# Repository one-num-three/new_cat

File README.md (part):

# 猫鼠行动 · 微信试点

## 小程序星露谷 16-bit UI 改版与上线前合规补齐（2026-11-27，前端本地完成）

完成微信小程序全页面视觉重构与上线前合规打磨（主包与 `room-tools` / `field-editor` 等现有分包，不改动服务端规则或 `hardware/`）：
- **星露谷 16-bit 像素 UI 与视觉细节重构**：建立统一像素木框/羊皮纸与夜间营火主题（`utils/sdv-theme.wxss`、`utils/sdv-borders.wxss`、`components/sdv-modal/`、`assets/sdv-v1/`），替换首页 3:2 像素头图并优化创建/准备/对局/导览/结算及分包页的层次、字号等宽数字、禁用按钮对比度与夜间模式可读性。
- **隐私合规与户外安全门禁**：移除首页冷启动自动读取剪贴板，改为用户手动点击粘贴并接入 `getPrivacySetting` / `requirePrivacyAuthorize` / `openPrivacyContract`；在创建房间、输入房间码加入与扫码加入前增加户外安全与隐私确认弹窗。
- **对局定位提示、残局清理与 7 日本地战绩页**：对局地图页增加“仅前台定位”提醒横幅及设置引导；首页自动清理已失效 `v2RoomId` 残留；新增分包本地 7 日战绩页（`room-tools/pages/history/`）并自动归档最近战绩；通过 `sitemap.json` 禁止索引调试台/标定等非业务页面。
- **验证范围与待验项**：本地 WXML/WXSS 编译、包体体积门禁（`rawLocalBytes.main < 1,500,000 B`，各分包 `< 2,097,152 B`）以及客户端/界面自动化回归通过；真机定位/相机/海报导出/安全区实测及微信开发者工具上传发布尚未执行。

## 猫鼠手环硬件 V1.5 EVT-A（2026-11-28，Strap-Halo 双版本 17 件 3D CAD + 磁吸四线 FPC + 4 层 KiCad 10 主板）

已完成 **EVT-A 机电变更同步**：包含 **Strap-Halo 腕带光环版双版本 17 零件参数化 3D CAD / Autodesk Fusion 360 工程（量产针扣版 + EVT `120–200 mm` 非对称低遮挡魔术贴简版）**、**磁吸四线 C 弯柔性转接板（0 ERC / 0 DRC，已导出打样 Gerber ZIP）**、**Strap-Halo 28.4×35.4 mm 四层 KiCad 10 主板工程（含 BLE 真实铣空槽）**、虚拟烧录仿真与产品报价分析（目录 `hardware/`）。
- **EVT-A 双版本 17 零件 3D CAD & Fusion 360 (`cad/output/CatMouseBand_V15_StrapHalo.step` · `CatMouseBand_V15_Velcro_Lite.step`)**：顶壳抬高 `+0.35 mm`（主机厚 `12.15 mm`，`ESP32-C3-MINI-1` 上方留 `0.80 mm` 净空至 NFC 铁氧体）、主板开真实 BLE 天线铣空槽（`X ∈ [-8.9, +5.5], Y ≤ -12.15`）、闭合 Hirose `FH19C-4S-0.5SH(10)` 4-Pin ZIF 与 `2.50×0.20×3.60 mm` PI 补强舌、完整建模 `17_Pogo_Flex_Interposer` 绕开 `1027` 马达（最小名义间隙 `0.125 mm`）。两版均通过 **17/17 合法 B-Rep 与 `0.000 mm³` 零碰撞校验**（针扣版 `33.06 g` / 魔术贴简版 `35.07 g`，后者实现 `136–200 mm` 腕围 `0%` 零遮光）。
- **EVT-A 磁吸四线 FPC (`pcb/catmouse-band-v15-pogo-flex/`)**：4 线（5V / GND / USB D− / D+）绕开马达，ERC=0、DRC=0、未连通=0，已导出工程打样资料 `Pogo-Flex-EVT-A-Gerber.zip`。
- **EVT-A 四层主板 (`pcb/catmouse-band-v15-strap-halo/`)**：与 3D 共享 `strap_halo_geometry.py` 轮廓，ERC=0，固件物理引脚 13/13 一致（尚有 10 项布线与 17 项阻值配料待闭合后投板）；已将 `hardware` 纳入 `project.config.json` 打包忽略项，不影响现有小程序主包。

入口：[硬件总览](hardware/README.md) · [EVT-A 机电变更记录](hardware/docs/Strap-Halo-EVT-A-机电变更.md) · [PCB 与 3D 结构协同布局规范](hardware/docs/PCB与3D结构协同布局规范.md) · [3D CAD & Fusion 360 双版本工程](hardware/cad/README.md) · [EVT-A 内部连接微距详图](hardware/cad/renders/cad_06_fpc_connection_detail.png) · [ECAD/MCAD 布局蓝图](hardware/cad/renders/cad_05_ecad_mcad_layout_blueprint.png) · [120–200mm 魔术贴遮盖分析图](hardware/cad/renders/cad_velcro_02_wrist_occlusion_analysis.png) · [磁吸四线 FPC 打样包](hardware/pcb/catmouse-band-v15-pogo-flex/Pogo-Flex-EVT-A-Gerber.zip) · [EVT-A 主板检查报告](hardware/pcb/catmouse-band-v15-strap-halo/review/audit.json)。

## 当前位置与后台授权（2026-11-04，前端修订）

通用范围编辑首次打开/切换地图时优先居中本人，拒绝定位仍可手动框选；已有集合点和手动操作不被迟到GPS覆盖。对局显式申请前台及后台定位授权，拒绝/接口不可用时降级前台。234项回归与编译/发行目录核验通过。[当前前端与真机待验步骤](reports/2026-11-04/current-location-background-v1/README.md)。账号后台接口仍需开通；本轮未微信上传或宣称真机锁屏通过。下方保留历史记录。

## 通用微信实时地图（2026-11-04，本地实现）

创建活动可直接点“使用实时地图”，选集合点并框选多边形，不再要求预制美术图或校区标定；原生对局地图支持现有角色授权、扫码抓捕、结算和轨迹导出。230项测试通过，前后端需配套部署。Git分支`codex/general-native-map`。[使用与验证说明](reports/2026-11-04/native-map-v1/README.md)。

## GPS精度放宽至50米（2026-10-23，已部署）

正式服务器已切换GPS50修订，版本仍0.6.1，准备/抓捕精度门槛≤50米。5秒新鲜度、双方坐标距离≤50米及动态码保持。公网健康检查与隔离PG验收通过；前端文案需重新编译/上传。[部署证据及最新前端目录](reports/2026-10-23/gps-threshold-50-v1/README.md)。

## 0.6.1 已部署与移动界面修订（2026-10-23）

后端0.6.1已上线，228项回归与模板/样式编译通过；修正定位信号宽度、按钮对齐、长文字、小屏大字号和安全区。完整前端：`reports/2026-10-23/deploy-0.6.1-v1/frontend-final/MODIFIED_FILE`。微信上传待开发者工具内确认，尚未公开发布；[交付与48张截图](reports/2026-10-23/deploy-0.6.1-v1/README.md)。下方保留历史状态。

## GitHub代码同步（2026-10-23）

当前代码包含候选API0.6.1及微信端的轨迹海报、保存/转发、鼠队视野共享、定位质量小信号，前后端保留在同一个仓库。本轮重新运行227项自动回归全部通过；[同步前验证](reports/2026-10-23/github-sync-v1/verification.json)。GitHub代码同步不等于服务器部署或微信上传；真机室外定位、相册保存/发送等仍需设备验证。以下保留各轮历史记录。

## 定位质量小信号（2026-10-22，本地完成）

地图/准备页增加四格定位指标与`±12m`精度估计，点开可查看原因：≤5/≤10/≤25/>25米依次4/3/2/1格；过期、权限、网络等灰显。25米服务端校验和5秒位置有效期保持，不新增定位请求。227项回归通过；[显示预览与验证](reports/2026-10-22/location-signal-v1/index.html)，非微信截图，真机待验。最新完整前端reports/2026-10-22/location-signal-v1/release-verified/MODIFIED_FILE；本次未部署或上传。

## 海报保存与转发（2026-10-22，本地完成）

结算→本人轨迹→生成海报；底部固定保存相册/转发入口，支持点图预览、长按操作。取消、权限失败和成功均有反馈；原生菜单使用期间保留临时文件，切页/身份变化防旧回调。220项回归通过，手机相册/实际发送仍未验；本次未部署或上传。[可保存的模拟轨迹PNG及验证](reports/2026-10-22/poster-save-share-v1/index.html)。最新完整前端：reports/2026-10-22/poster-save-share-v1/release-verified/MODIFIED_FILE；API仍为本地候选0.6.1，历史记录如下。

## 最新候选0.6.1：轨迹亮点（2026-10-21，未部署/上传）

本人轨迹海报新增透明起终点旗子、“跑得最快”和鼠身份的“离猫最近”真实数据气泡；位置由有效记录计算，不预画。近猫摘要由服务端赛后授权派生，普通玩家不收到猫坐标或隐藏路线。数据不足省略。

最新四张左右透明气泡已接入，并修正起点遮挡：亮点后画旗子，气泡按完整旗框优先换向、再移位，文字/旗子零交叠。216项回归通过，三地图六面旗像素校验通过。[最新对照预览](reports/2026-10-21/track-highlights-layer-v2/index.html) · [代码/验证说明](reports/2026-10-21/track-highlights-layer-v2/README.md)。微信原生页面仍未验收（上一轮工具受阻，本修订未重试）；预览为桌面Canvas，非微信截图/真人记录。完整前端：`reports/2026-10-21/track-highlights-layer-v2/release-verified/MODIFIED_FILE`。旧交付保留，下方0.6.0为历史记录。

## 最新本地候选0.6.0（2026-10-21，未部署/上传）

新增房主“鼠队视野共享”设置、赛后本人/房主全员轨迹导出，以及用户确认的不规则草地边框海报（玄武湖、九龙湖、四牌楼）。使用真实本局记录，不预画路线或套用示例数字；地图等比，原画保留。开局冻结设置/标定，历史结果不覆盖。

入口：房间→玩法设置；结算→我的行动轨迹与导出→生成我的轨迹海报。当前线上0.5.2不支持新接口，须前后端配套升级。

[使用规则和现场步骤](TRACKS_AND_TEAM_VISION.md) · [实际微信预览](reports/2026-10-21/tracks-team-vision-v1/index.html) · [启动与验证记录](reports/2026-10-21/tracks-team-vision-v1/README.md)。最终完整前端目录：`reports/2026-10-21/tracks-team-vision-v1/release-verified/MODIFIED_FILE`。209项回归通过；真机保存/分享、后台权限及新公网压测未验。下方内容为各轮历史记录。

## 代码质量复核（2026-10-21）

地图原图保留，按用户决定不处理单张图片200 K建议项。已开启组件按需注入，微信工具重新扫描该项通过；字体原始字节不变，改为app.wxss全局声明。主包原始文件989,713 B；微信依赖分析约943 KB，但质量面板的1.5 M项仍未通过，原因尚未确定，不把源码统计当成平台通过。用户决定停止追查该提示。

当前完整前端目录：`reports/2026-10-21/package-quality-v2/release/MODIFIED_FILE`，包含app.wxss和全部分包。196项回归及逐入口编译通过；本轮没有上传或发布。[复核记录](reports/2026-10-21/package-quality-v2/README.md)。下方为历史记录。

## 主包已降至约0.99MB（2026-10-21，本地完成）

工程及最终目录包主包原始文件均为989,574B，低于更严格的1,500,000B上限，余510,426B。玄武湖原图按需分包，图片尺寸/字节/标定SHA与美术不变，根文档和未引用旧API不再上传；打包与回归增加主包硬门禁和运行依赖核验。196项回归、17WXML/21WXSS编译、微信MCP冷加载创建页/玄武湖/九龙湖及切回通过。不是微信上传后包体或真机公网下载验收，本轮未上传、发布或部署。

工程仍打开根目录。最新完整前端目录：`reports/2026-10-21/main-package-v1/release-verified/MODIFIED_FILE`，需要保留所有分包。[体积、截图与复核命令](reports/2026-10-21/main-package-v1/README.md)。以下日期条目保留历史状态。

## 本地新增：对局后台定位（2026-10-20，API 0.5.3 候选）

已接微信后台定位：本局参与期间切后台保留定位和授权连接；被捕、退出、取消或终局后停止；返回前台保持同一身份和对局，不重复启动轮询。权限不足时明确降级为前台模式。新增对局绑定的位置样本门禁，无表迁移，猫鼠行动规则不变。

193/193 回归、官方编译及 MCP 隐藏/恢复/被捕清理验证通过；MCP 模拟后台授权和生命周期，不代表真机锁屏通过。**用户确认账号尚未开通 startLocationUpdateBackground，线上仍 0.5.2，本候选未部署或上传。** 配置入口、目录包、截图和权限获批后的手机测试见 [后台定位交付](reports/2026-10-20/background-location-v1/README.md)。下方各日期记录保留历史状态。

## 当前服务：API0.5.2已部署（2026-10-19）

真实HTTPS/WSS已更新为0.5.2，支持reinforce-v2动态捕获目标、fresh-v1重新准备及认证快照viewerId。原房间/会话保留，切换前0活跃局；数据库备份已独立恢复核验。当前微信工程及配套前端目录版同步为本次源码，测试身份关闭。微信开发版本上传状态以 [本次部署证据](reports/2026-10-19/deploy-0.5.2-v1/README.md) 为准；正式审核发布须区分记录。

运行工程仍为 `D:\cat-mouse-miniprogram`，目录交付为 `reports/2026-10-19/deploy-0.5.2-v1/frontend-final/MODIFIED_FILE`。下方“尚未部署”描述保留其历史日期状态，由本节接续。

## 最新本地增量：动态捕获目标（2026-10-19，API 0.5.2）

中途补员采用 **reinforce-v2**：捕获目标始终为本局累计加入的鼠人数的60%，向上取整。标准8人2猫6鼠开局为4；第9人补鼠后为5，第10人补猫后仍为5；补到12人3猫9鼠后为6。右上角分母由同一服务端事务更新，经授权WebSocket同步给所有人，断线恢复使用最新快照。原阵营和本局截止时间不变。

入房成功即计入，30秒内定位入场；被捕、主动退出、入场超时和断线均不减少累计鼠人数，原身份重连不重复增加目标。已确认终局不因后来的加入而重开或改写。新增猫更新人数，鼠人数未变时60%规则的目标保持不变。此规则覆盖历史 reinforce-v1 的固定目标约定，仍是待场地验证的试点参数。

本地使用原启动方式与数据库，无表迁移；线上仍0.5.0，本轮不部署或微信发布。验证与MCP截图见 [动态目标说明](reports/2026-10-19/dynamic-target-v1/README.md)。下方各轮说明保留历史语义。

## 最新本地验证：扫码抓捕、全员结算与下一局（2026-10-19，API 0.5.1）

微信MCP已完成标准8人局：4次实际动态码PNG解码后的模拟扫码、8人一致猫胜、全员重新定位准备、新matchId及8人新阵营。21张原图逐一核对服务端viewerId、房主标志、角色、状态、进度与胜负；旧结果保持唯一且未覆盖。**181/181回归通过**，编译通过。[截图图集](reports/2026-10-19/mcp-capture-replay-v1/index.html) · [复现与验证范围](reports/2026-10-19/mcp-capture-replay-v1/README.md)。

修复终局旧ready残留、普通玩家无法回准备、抓捕提示被快照清除和旧会话快照/响应串入。新开局仍只允许房主；本地0.5.1新增fresh-v1准备约束及认证快照viewerId。**线上仍0.5.0，本轮修复尚未部署，前端未上传发布**。本次1个模拟器＋8条授权WS、模拟GPS/相机回传，不代表真机相机或公网验收。

## 当前交付：中途补入猫鼠与全员同步（2026-10-19）

本次新增微信MCP完整复验：标准8人开局后补入2人，10个授权连接的角色、状态和公共名单一致，已取得10个身份各自的实际页面截图；P09断线→失联暂停→原页自动重连→被捕房主恢复均通过。修复被捕房主恢复和旧会话快照保护，当前回归 **177/177**。本轮为1个模拟器＋10个WS、模拟GPS、本机隔离PGlite，不代表10台真机或公网验收。[本轮图集](reports/2026-10-19/mcp-join-reconnect-v1/index.html) · [复现方法与证据](reports/2026-10-19/mcp-join-reconnect-v1/README.md)。前端仍需本地编译预览，尚未上传发布。

后端 **0.5.0 已部署**。开局后新玩家按开局比例补入猫或鼠，30秒内定位入场；老玩家不重抽，开局捕获目标和截止时间不变。断线回来保留原阵营及被捕/退出状态，不能重进入房复活。新增试点策略登记为 reinforce-v1，基础pilot-0.3保留。

准备页和地图页共用实时WebSocket、断线轮询与重连；名单、阵营、在线/入场/出局、进度及结果统一同步，位置仍按权限裁剪。此前175项基线回归通过，真实PostgreSQL完成8人开局＋2人补入、10个授权WS一致快照；最新177项及MCP复验见上段。真机/现场平衡和本轮新负载验收未执行，前端尚未发布。

[本轮规则、配置与证据](reports/2026-10-19/late-join-sync-v1/README.md) · [微信MCP截图](reports/2026-10-19/late-join-sync-v1/index.html)。开发工具继续打开本仓库根目录并编译，真实房间码9D61CEDC51仍保留。

## 上一轮交付：真实地图服务、房间与邀请（2026-10-19，0.4.0）

后端 API **0.4.0** 已部署到 https://seu-link.fit/catmouse ，沿用真实微信登录与 PostgreSQL；正式默认8人2猫6鼠、捕获目标4，规则仍 pilot-0.3。服务端登记三处地图、修订与图层；房主可在开局前/终局后改校区、集合点、多边形范围。建房有持久化幂等回执，抓捕凭据绑定对局/目标/有效期并原子确认，超时可用同指令重试。

微信开发工具打开本仓库根目录。首页新增“扫码加入”，准备页提供微信分享与真实邀请二维码。普通邀请二维码须在本小程序内扫描，不是外部微信启动码。当前前端尚未上传/发布，手机需预览本工程。真实MCP联调房间码 **9D61CEDC51**，当前1/8人、未开始；没有向联系人发送分享。

173项回归通过，真实PostgreSQL隔离验收14项、备份恢复成功；官方16WXML/20WXSS编译通过。微信MCP已验证真实登录/建房/范围保存/邀请码解码和一次授权WSS联通，修复实际编辑面板裁切。真机相机、GPS、公网长时联机、微信上传包体仍待验。

完整启动/配置、截图、目录版交付与真机步骤见 [本轮说明](reports/2026-10-19/real-rooms-v1/README.md) 和 [MCP图集](reports/2026-10-19/real-rooms-v1/index.html)。以下旧章节保留各自日期与当时验证结论，当前状态以本节和RELEASE顶部为准。

## 集合点与多边形范围初始增量（2026-10-19，已由0.4.0接续）

- 创建活动 → **地图框选范围**；已有房间由房主点 **修改集合点与范围**。在真实地图依次选3–16个顶点，单独选集合点；点编号后可移动顶点，支持撤销/删除/重画、地图平移和缩放。
- 开局前或终局后可改；进行中和暂停时锁定。保存到服务端后全员重新定位、准备。原圆形场地兼容；新多边形同时用于越界裁决及原生/艺术/3D地图显示。
- 开发调试台新增「集合点与多边形 · 开发预览」，只验证交互，不读取GPS或提交服务器。
- 后端需 `/api/version` **0.3.3 / polygonVenues:true**；本轮仅本地实现，未部署或上传。使用与验证边界见 [交付说明](reports/2026-10-19/venue-boundary-v1/README.md)。

## 仓库结构与独立部署

前后端在同一仓库维护，分别运行和部署，保持接口、地图参考和规则变更同步：

| 目录 | 用途 |
| --- | --- |
| 根目录的 `app.*`、`pages/`、`components/`、`utils/` | 微信小程序；开发者工具打开仓库根目录 |
| `cat-mouse-server/` | 后端服务、共享规则/坐标模块与自动化回归；Docker构建目录也在这里 |
| `assets/`、`campus3d/`、`venue-maps/` | 客户端运行素材与按需资源分包 |
| `design/` | 设计原件、许可、地理参考及回归依赖；保留原始字节供SHA校验 |
| `scripts/`、`reports/` | 构建工具、审计与验证说明 |

GitHub同步保留源码、测试和必要原件；本机密钥、数据库、依赖缓存、压缩归档、重复交付副本与报告截图通过`.gitignore`排除，仍留在本地。报告中的历史截图/交付路径可能仅在原工作目录可用。真实配置从环境变量或未跟踪的`.env`加载，示例见`cat-mouse-server/.env.example`。后端独立部署不要求把微信前端放到服务器。

## 2026-10-19 · 微信日志排查与 3D 首次加载修复

模型描述改为可读取的 `campus3d/assets/campus-meta.bin`（UTF-8 JSON 内容），修复重新编译后 3D 加载失败；四个业务页补齐首帧字体参数。最新修复、重新编译后的实际截图与回归见 [排查记录](reports/2026-10-19/wechat-permission-diagnostics-v1/README.md)。此记录补充并更新下方首版 3D 交付；未上传或部署。

## 九龙湖 3D 视图更新 · 2026-10-19

当前工程已增加九龙湖第三种可切换视图：**像素地图 / 实时地图 / 3D校园**。打开本目录，编译后进入「场地地图→九龙湖→叠层图标→3D校园」；对局页也有同一入口。单指平移、双指缩放旋转，准星回到本人。3D 需要首开加载本地资源分包，真机仍需允许定位。

3D 使用提供的「已建与在建、去规划」Blender 模型，并有独立的近似定位参考；不是实测建筑/高度地图。原像素图及其控制网保留。模型说明见 [模型 README](design/models/jiulonghu-blender-v1/README.md)，验证记录见 `reports/2026-10-19/jiulonghu-3d-v1`。本次不修改服务端猫鼠行动规则，也未发布、上传或部署。

## 2026-10-18 九龙湖全校参考覆盖 v3

当前运行模型补齐外围8个道路路口/桥端参考点，共31控制点、53分区，完整覆盖保存的OSM校园多边形。运行投影检查86个独立校界顶点、沿界约5米采样和校内10米网格，无遗漏或图外位置；原23地标和梅园反馈坐标保持。模型与原画不等于实地测量，`fieldVerified=false`；定位覆盖边界也不是猫鼠行动活动范围。边界图、复核命令与证据见 [本轮说明](reports/2026-10-18/jiulonghu-campus-coverage-v3/README.md)。重新编译小程序即可使用，手机仍读取真实GCJ-02定位。

## 2026-10-18 九龙湖梅园定位覆盖修复

已复现并修复梅园7B附近“校区内却提示图片配准范围外”：补3个OSM/原画地标，将九龙湖控制网扩为23点/36分区，原画不变。开发调试台新增「九龙湖 · 电脑模拟本人定位」，仅电脑开发工具启用，明确标记模拟；手机仍采实际GPS。139项回归通过；详情与截图见 [本轮记录](reports/2026-10-18/jiulonghu-location-fix-v1/README.md)。

## 2026-10-17 地图余量与真机本人定位

艺术地图四边增加停留余量、阻尼与220ms回弹。「首页 → 场地地图」右上准星可主动开启真实本人定位，显示精度/GCJ-02坐标；图层切换真实地图，关闭图标停止。无需开房，位置仅本机显示；对局仍使用服务端授权状态。135项回归、官方编译通过；当前C盘0空间导致微信预览白屏，真机/手势与现场GPS尚未验收。操作与证据见 [本轮说明](reports/2026-10-17/map-margin-gps-v1/README.md)。

## 最新接入：三处场地地图（2026-10-17）

创建活动可选玄武湖、东南大学九龙湖、东南大学四牌楼。切换地图须重新确认现场集合点；既有房间默认玄武湖。首页「场地地图」提供公共导览，开发调试台另有两校区定位演示（模拟数据）。地图保持等比、缩放拖动、透明标记和贴边图标面板。

校区底图与参考配准已接入；两张原PNG及交接资料保持原样，**真实GPS精度尚未实地验收**。手机输入GCJ-02，显示层近似转换到WGS84三角网；房间实地标定优先、覆盖外不外推。

本轮130项回归通过，官方12份WXML/16份WXSS编译通过。交付、截图与复核步骤：[校区接入说明](reports/2026-10-16/campus-integration-v1/README.md)。后端须同步更新，`/api/version` 应为0.3.2且 `capabilities.multiVenueMaps=true`；此次没有部署线上服务器。

## 2026-10-13 沉浸地图 v4

地图导览改为单张放大的图片等比cover铺满，不再保留蓝色空条和底部大工具栏。内置生图按v3原稿扩绘湖面，实际生成1254×1254；运行JPEG804062B，原PNG和v3均保留。每7.5秒沿矩形四角缓慢平移，每个完整四周环路约30秒，首次另有中心进入过渡。任意触摸即暂停自动运动，用户可拖动、双指缩放或用小控件1–4倍缩放；放手不自动抢回镜头，只有点“巡游”恢复。隐藏/离页停止计时器，同尺寸布局不扰动手动镜头。

原生IDE已实测自动图像位置变化、触摸打断、单指拖动、双指缩放、停留、居中及恢复9项。此艺术图未地理配准，真实对局继续授权原生map。新证据见reports/2026-10-13/map-immersive-v1/。生图原始提示词及SHA见design/maps/xuanwu-lake/immersive-v4/；源码改动不改变pilot-0.2、身份或胜负。

---

## 当前增量实现（2026-10-13，pixel-native-final-v2）

修复：原生组件选择器不再允许空检查通过；按钮从首帧预留原稿尺寸，图片异步加载后地图重测可用空间，不裁边、不拉伸；无尺寸变化时保留缩放。79项自动回归通过；MCP正常/大字/窄内容各17张截图，窄版仍是320×693内容约束而非真机。24项累计预览交互断言已通过，包括原生触摸平移、缩放、错误重试、入房/准备/开始及安全区内的页尾动作。大字关闭最终通过原生子按钮点击和MCP状态读取补验；证据来自分段运行，不冒充单次整批成功。

最新无压缩小程序副本与证据：reports/2026-10-13/pixel-native-final-v2/。图库/15状态入口不变；真实身份、定位、抓捕及胜负逻辑不变，本轮没有上传或改服务器。旧截图的空组件几何检查不作最新版验收依据。

面向 6–12 名熟人的实景猫鼠短局。微信小程序是本轮主客户端；服务端统一身份、阶段、抓捕和结算。规则版本为 `pilot-0.2`，具体数值是场地试点参数，尚未验证平衡性。历史冻结规划见 [PROJECT_PLAN.md](PROJECT_PLAN.md)，2026-10-08 审计仍保留在 `reports/`。

当前视觉基线为用户交接的晴日公园 16-bit 像素 15 状态，已替换到原生小程序；02-01 外观保留为历史。组件、字体、素材与比例约束见 [DESIGN_BASELINE.md](DESIGN_BASELINE.md)。

已选素材及其 SHA-256、运行副本与未来生图提示词固定在 [ART_LOCK.md](ART_LOCK.md)。运行地图的被捕、暂停/重连与胜利状态已使用相应插画；未来技能视觉仍是概念素材，不是已启用玩法。

可复用透明插画、已接入地图的标记和分层页面源文件见 [素材说明](design/2026-10-09/usable-assets/README.md)。

## 新 UI 预览（2026-10-13）

微信开发者工具导入 `D:\cat-mouse-miniprogram`，编译模式选择「界面调试台」，逐项打开状态；「玄武湖新版地图」可独立打开完整导览。原设计参考入口仍是 `design/2026-10-12/pixel-day-replica-v1/index.html`，这是设计对照，不是业务客户端。当前6个注册页面复用真实处理器；开发预览使用固定数据，不发起对局/GPS/抓捕请求。

代码回归75/75，素材哈希通过，33文件隔离回滚及旧31测试通过。可复核证据：`reports/2026-10-13/xuanwu-ui-v1/VERIFICATION.txt`；逐页对照：同目录 `visual/compare.html`。修前完整IDE截图已有51张；最后6项细节修复后整批截图/交互因C盘空间为0未完成，腾出空间后重新编译并运行下列脚本。真实手机/系统大字/GPS配准/扫码仍单独验收。

无压缩导出：`powershell -File scripts/package-release.ps1 -DirectoryOnly -OutputDirectory <新的空输出目录>`，输出MODIFIED_FILE文件夹；保留所有源素材，不上传或部署。

## 本地启动

需要 Node.js 22+。服务端默认使用持久化的嵌入式 PostgreSQL（PGlite），数据目录为 `cat-mouse-server/data/`。两身份工程验收时，在 PowerShell 中运行：

```powershell
cd D:\cat-mouse-miniprogram\cat-mouse-server
npm ci
$env:NODE_ENV='test'
$env:ENABLE_LOCAL_TEST_IDENTITIES='true'
npm start
```

访问 `http://127.0.0.1:4000/health` 和 `/ready`。`/api/v2/session/test` 只在上述显式本地测试模式启用。切回真实微信登录时，清除这两个环境变量，在服务端配置 `WECHAT_APP_ID`、`WECHAT_APP_SECRET`，并将小程序 `utils/config.js` 的 `localTestIdentities` 改为 `false`。正式部署必须配置 `DATABASE_URL`；没有它，`NODE_ENV=production` 会拒绝启动。

微信开发者工具导入仓库根目录。当前 `project.config.json` 已填写试点 AppID；`utils/config.js` 指向 `https://seu-link.fit/catmouse` 和 `wss://seu-link.fit/catmouse`，并使用真实 `wx.login`，不会请求测试身份接口。测试身份模式仅用于上面的隔离本地服务端验收；若要从小程序连接本地服务，需临时修改 `utils/config.js`，测试结束后恢复当前公网配置。2026-10-11 已巡检开发工具 390×753 视口的调试台及 14 个页面/状态，并修正实际渲染问题；真实登录、手机定位/扫码、小屏和大字体仍待真机验证。

## 开发版界面调试台

以开发版在微信开发者工具打开小程序首页，点击「打开界面调试台」；也可在工具顶部编译模式下拉框选择「界面调试台」或任一状态并重新编译。`project.config.json` 已登记 16 个编译模式（调试台 + 14 个页面/状态 + 玄武湖导览）。可单独打开首页、创建、房间准备、猫/鼠追逐地图、近距预警、躲藏、动态码、被捕、暂停、断线、两种胜利和取消。调试台使用显著的「界面预览」标记与固定样例数据；动态码为不可扫描的占位图。进入预览不会调用会话、房间、定位、相机、WebSocket 或定时同步，也不会改动真实对局。预览内的创建、准备和开局只在界面本地切换或跳转，返回后可选择下一项；真实流程仍从首页正常按钮进入。该入口仅在小程序 `envVersion=develop` 出现，体验版/正式版直接打开预览链接会回到首页。

本地两身份流程：各自建立测试会话 → 一个创建 2 人工程房间 → 另一人输入房间码加入 → 两人定位准备 → 房主开始 → 30 秒躲藏 → 鼠展示 15 秒动态码 → 猫扫码 → 两端看到猫胜。正式预设仍为 6–12 人，8 人为 2 猫 6 鼠。

### 不移动桌面窗口的自动巡检

用户已在本机 IDE 开启服务端口。开发工具保持现有分屏；以下命令只控制小程序路由，不上传或发布，也不调整窗口。先 `cd cat-mouse-server; npm ci; cd ..` 安装开发依赖，正式镜像继续 `npm ci --omit=dev`。

```powershell
& 'D:\Program Files (x86)\微信web开发者工具\cli.bat' auto --project 'D:\cat-mouse-miniprogram' --auto-port 9420
node scripts/replica-review.cjs all "$env:TEMP\cat-mouse-faithful-v2\normal"
node scripts/replica-review.cjs all "$env:TEMP\cat-mouse-faithful-v2\large" large
node scripts/replica-review.cjs all "$env:TEMP\cat-mouse-faithful-v2\narrow" normal 320x693
node scripts/replica-interaction.cjs "$env:TEMP\cat-mouse-faithful-v2\interaction"
```

巡检校验预览身份、各页边界、地图面板不重叠、房间码/复制按钮分离、冻结/出局/断线文案和素材实际渲染比例。`onResize` 配合同源生成的 `utils/art-ratios.wxss`，避免 widthFix 在改宽时缓存旧高度；不使用单轴拉伸。本轮使用官方SDK路由/选择器与截图，没有桌面窗口调整。中间证据先放项目外，减少IDE文件监控触发重编译的干扰；SDK可能显示截图缩略图，未声称修复IDE窗口自行缩小。320x693仅改变页面布局画布，不是实际320px设备或系统分辨率测试。截图合集保留每张来自哪次顺序采集，不描述为最后一次全量重跑。逐页比对见 [原稿与三种布局](reports/2026-10-12/replica-v2/visual/compare.html)，命令与原始结果见 [当前复刻证据](reports/2026-10-12/replica-v2/VERIFICATION.txt)。

## 规则与架构

- 30 秒躲藏、6 分钟追逐。猫达到开局鼠人数 60% 向上取整的抓捕目标即胜；截止时未达目标则鼠胜。取消不计胜负。
- 猫每 30 秒得到存活鼠约 50 米区域线索；鼠在猫进入约 120 米范围时只收到近距预警，不收到猫坐标；被捕者只看公开状态。客户端不会收到全员精确坐标。
- 停下扫码是抓捕动作。服务端绑定对局、鼠身份和 15 秒有效期，原子消费；最近 5 秒、精度 ≤25 米、距离 ≤50 米的 GPS 仅作辅助校验，线下仍需近距确认。
- 房间、会话、命令结果、事件、历史结果存 PostgreSQL；最新位置只在单进程内存。重启后进行中对局暂停，必须重新采集位置，由房主恢复。
- REST `/api/v2` 承担可靠命令；原生 WebSocket `/api/v2/live` 推送逐人授权快照。断线降级为单飞轮询。旧 `server.js` 留作审计来源，不是启动入口，也不随发布包复制。
- 地图页 WebSocket 断开后继续每 2 秒读取授权快照，并按退避间隔重连；正常连接每 1 秒推送一次授权快照，离页清理重试、心跳和定位。定位事件最短约 2 秒上报一次，事件缺失时约 3 秒补采样；真正的定位回调频率、精度和端到端可见延迟仍需真机验证。

## 验证

```powershell
cd D:\cat-mouse-miniprogram\cat-mouse-server
npm test
cd ..
node cat-mouse-server/v2/load60.cjs reports/2026-10-09/evidence/load60-location-fast-local.json
powershell -ExecutionPolicy Bypass -File .\scripts\package-release.ps1
```

自动化测试涵盖身份、权限、人数、动态码、时间、并发、可见性、数据库写失败、重启恢复和旧结果保留。60 人脚本包含每 2 秒位置上报、状态读取、WebSocket 推送及部分重连；默认仍是本地嵌入式数据库仿真，不代表真机、公网或自有服务器容量。当前证据与未执行项目见 [WORK_LOG.md](WORK_LOG.md)。部署和真机试点见 [RELEASE.md](RELEASE.md)。

## 2026-10-13 全页字体与可配置人数
- 六个已注册页面和公共组件采用Fusion Pixel12px比例简中版，字重400；实时按钮文字不用旧PNG烘焙字。原插画/地图保持宽高比和原稿文字；昵称未覆盖字符后备字体。静态539字形/21640B，原字体与OFL锁定，运行目录附完整继承许可。人数输入静止时用像素值层，聚焦时保留真实原生输入/光标，不伪造可编辑控件。
- 创建页独立填写总人数、猫数、鼠数，默认8/2/6；正整数、各至少1人、加和相等；总数2–60为配置边界，不是并发或场地安全容量承诺。主试点仍6–12人。创建后锁定配置，不开放局中改阵营。
- 显式cats/mice登记pilot-0.3；旧total-only请求保留pilot-0.2。服务端人数分配与捕获目标使用已存配置，旧房间不迁移，历史结果不覆盖。细则RULES_PILOT_0_3.md。
- 验证：基线84/84，修改88/88；全部1770种有效组合和非法值矩阵；真实HTTP三身份自定义1猫2鼠，目标2，越权开始拒绝，规则/取消结果数据库持久化与重启恢复。微信IDE正常17状态，大字3/窄内容3及10/3/7自定义完整演示流程实际截图。后续静止输入字体/短位置按钮修正另有最终截图。大字为应用1.3，窄为390模拟器内320内容，真机另验。
- 自查：创建仍鉴权，禁止winner/role等未知字段，玩家管理权限不增加；并发/抓捕/截止/位置授权回归保持；前后端均校验数量；无新定位timer/监听，图片无轴向压缩，规则结果同源；没有线上发布或数据库变更。线上旧服务需同步后端后才支持新请求字段。
- 交付与命令证据：reports/2026-10-13/global-font-teams-v1。下一步：真机编辑光标/字号，更新服务器之后微信登录真实8人样例；人数配比尚未做场地平衡验证。

## 2026-10-14 图片与地理位置绑定
- 实施目标：把新版图的像素位置和GCJ-02位置关联，继续使用服务端授权视野，保持图片宽高与手势。实际地标数据暂缺，用户已明确稍后通过标定页采集；没有把旧WGS84锚点或模拟点当成实地成果。
- 实现：房主局外标定页，图片触点、真实地图中心/一次GPS采集、至少3控制+2独立核验点、残差与分布检查、按图片SHA绑定；本机草稿恢复，服务端JSONB原子保存/重启恢复，版本冲突和重复指令保护，保存后全员重新准备。原图不变形，点/区域与图片同一动画图层，滚动偏移纳入选点换算。
- 自查：身份来自原会话，非房主保存403，未知配置拒绝；局中修改禁止，旧版本冲突拒绝；只投影授权visiblePositions/intel，不取全员坐标；断线和捕获位置清理保持；无新定位循环，GPS只点采；规则pilot-0.2/0.3、赢家和动态码抓捕不改。共享算法单一源并校验发行副本，不扩模式。
- 验证：基线88/88；修改98/98。真实HTTP授权/并发同ID保存/版本冲突/重启恢复；UI原生模拟事件5项通过，缩放/平移标记与图片误差<2显示像素，模拟坐标非实测。首轮精确浮点相等断言已修正为容差。SDK结束事件丢失坐标(0,0)，改以按下位置判定静止轻点，取消/拖动不选点；SDK Page.callMethod上下文异常改为实际页面对象调用。新页长文滚动发现坐标偏移并补测。
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
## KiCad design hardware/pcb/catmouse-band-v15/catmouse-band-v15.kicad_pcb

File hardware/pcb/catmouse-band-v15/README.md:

# CatMouse Band V1.5 EVT — KiCad 10 4 层紧凑主板工程

本目录为 **KiCad 10.0 原生 4 层 PCB 工程**，所有原理图符号与 PCB 封装均已自包含嵌入，双击 `catmouse-band-v15.kicad_pro` 即可直接打开，无需安装任何第三方库。

## 文件说明

| 文件 / 目录 | 说明 |
|---|---|
| `catmouse-band-v15.kicad_pro` | KiCad 10 工程配置与嘉立创 4 层工艺约束 |
| `catmouse-band-v15.kicad_dru` | 自定义设计规则（最小间距 `0.127mm`、电源线宽、板边净空 `0.30mm`） |
| `catmouse-band-v15.kicad_sch` | 80 器件 / 55 网络完整原理图（5 大功能分区，官方 ERC 0 违规） |
| `catmouse-band-v15.kicad_pcb` | 40.0 × 46.0 mm（R=14mm）4 层紧凑主板（L1 发光环 / L2 完整 GND / L3 +3V3 / L4 核心芯片） |
| `catmouse-band-v15.net` | KiCad 10 官方导出网表（已与 EVT 固件 12 引脚校验 100% 对齐） |
| `erc_report.json` / `drc_report.json` | KiCad 10.0.8 官方 ERC 与 DRC 完整检查报告 |
| `fab_jlcpcb/` | 嘉立创 4 层打样生产包（11 层 Gerber + Excellon 钻孔 + SMT 贴片坐标 CPL + BOM） |
| `previews/` | KiCad 10 官方渲染的高清 3D 正面/背面/透视图 + 原理图 PDF + 分层 SVG |

## 嘉立创 4 层打样推荐参数

- **层数**：4 层（`F.Cu` / `In1.Cu` / `In2.Cu` / `B.Cu`）
- **板厚**：`1.0 mm`（叠层 `JLC04101H-7628`）
- **表面工艺**：**沉金（ENIG）**（推荐，保证背面 4-pin 磁吸充电烧录触点长期插拔耐磨）
- **阻焊颜色**：哑光黑（提升正面 12 颗 `WS2812B-2020` 发光环在白天户外的高对比度！）
- **过孔覆盖**：过孔盖油（标准免费工艺，最小过孔 `0.20 / 0.45 mm`）

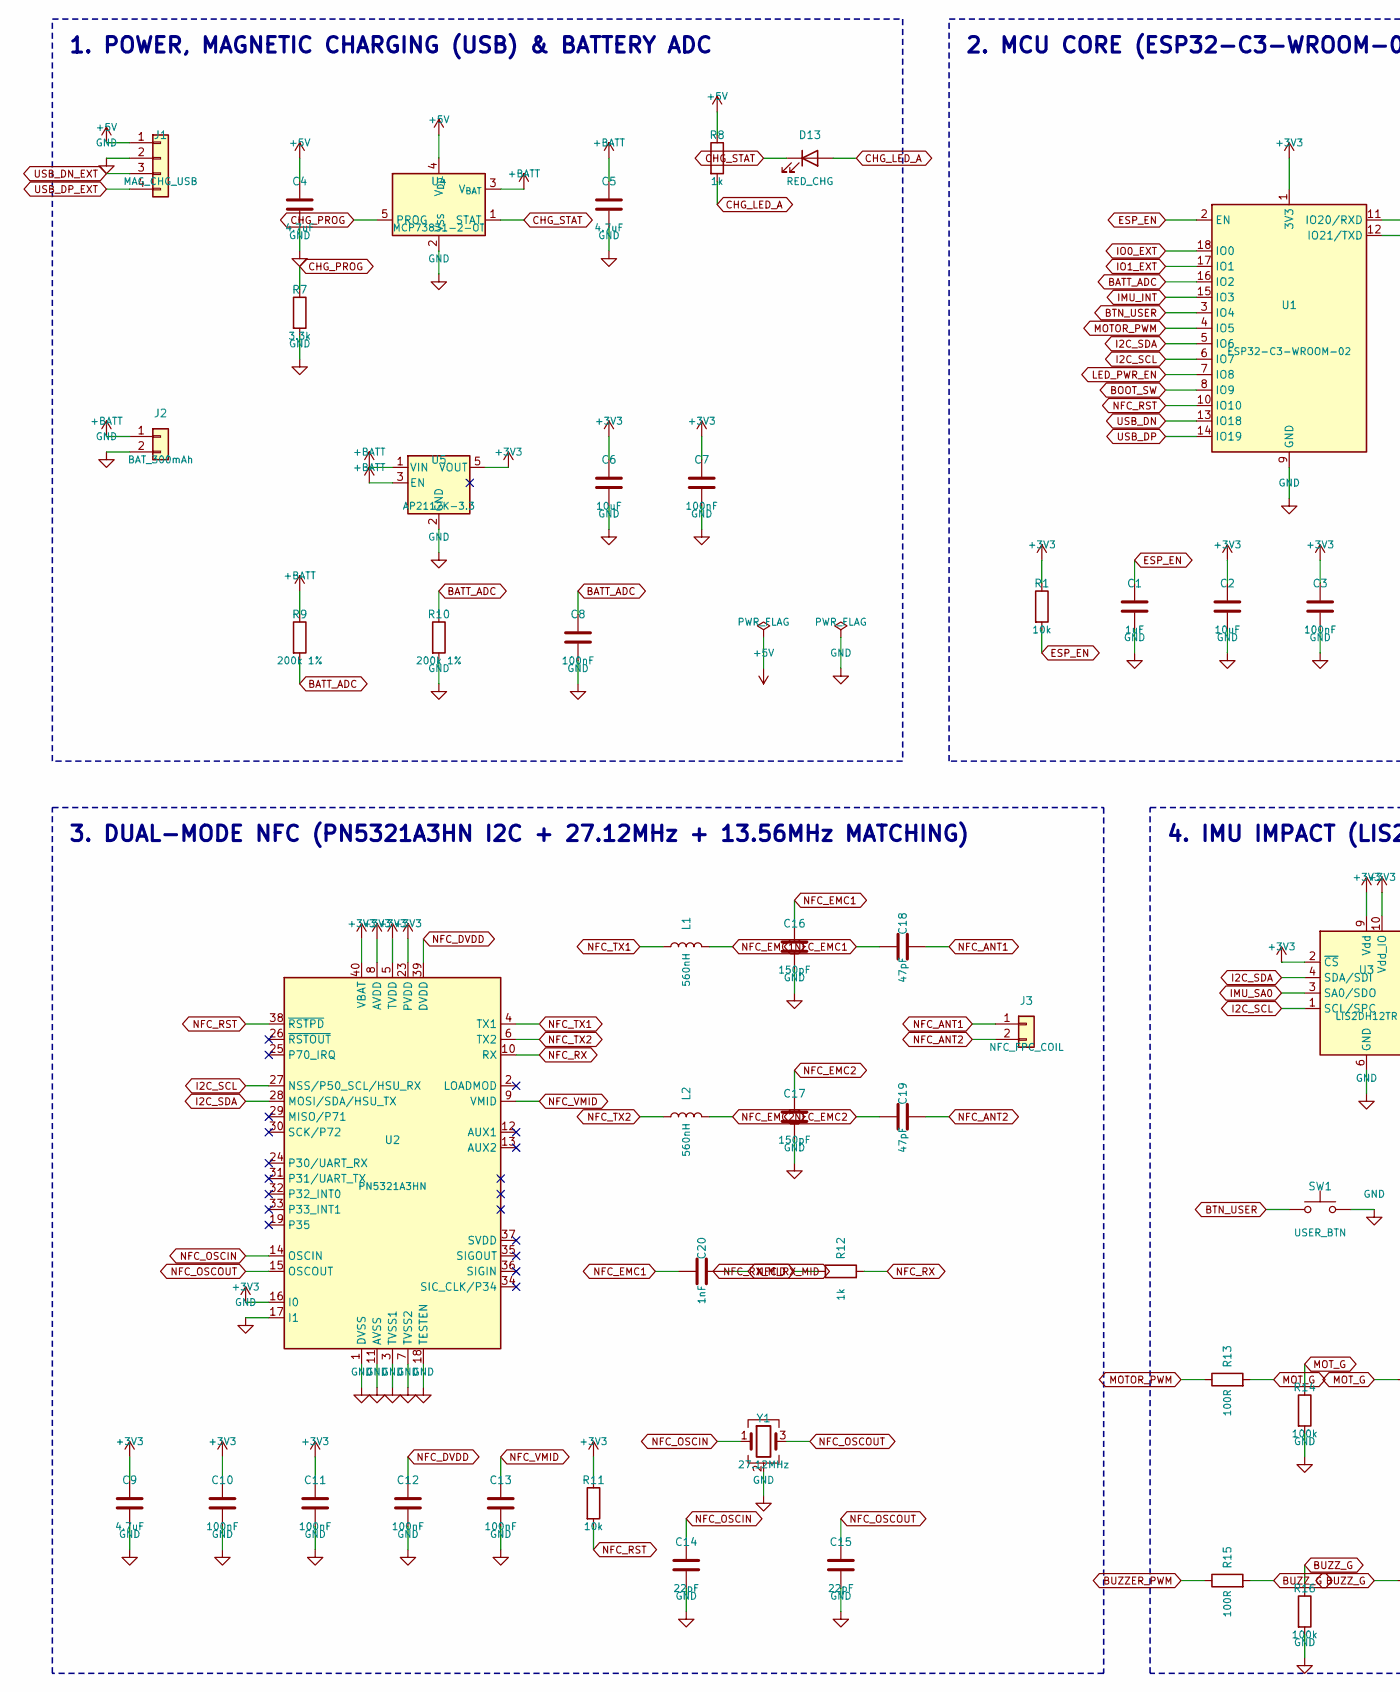
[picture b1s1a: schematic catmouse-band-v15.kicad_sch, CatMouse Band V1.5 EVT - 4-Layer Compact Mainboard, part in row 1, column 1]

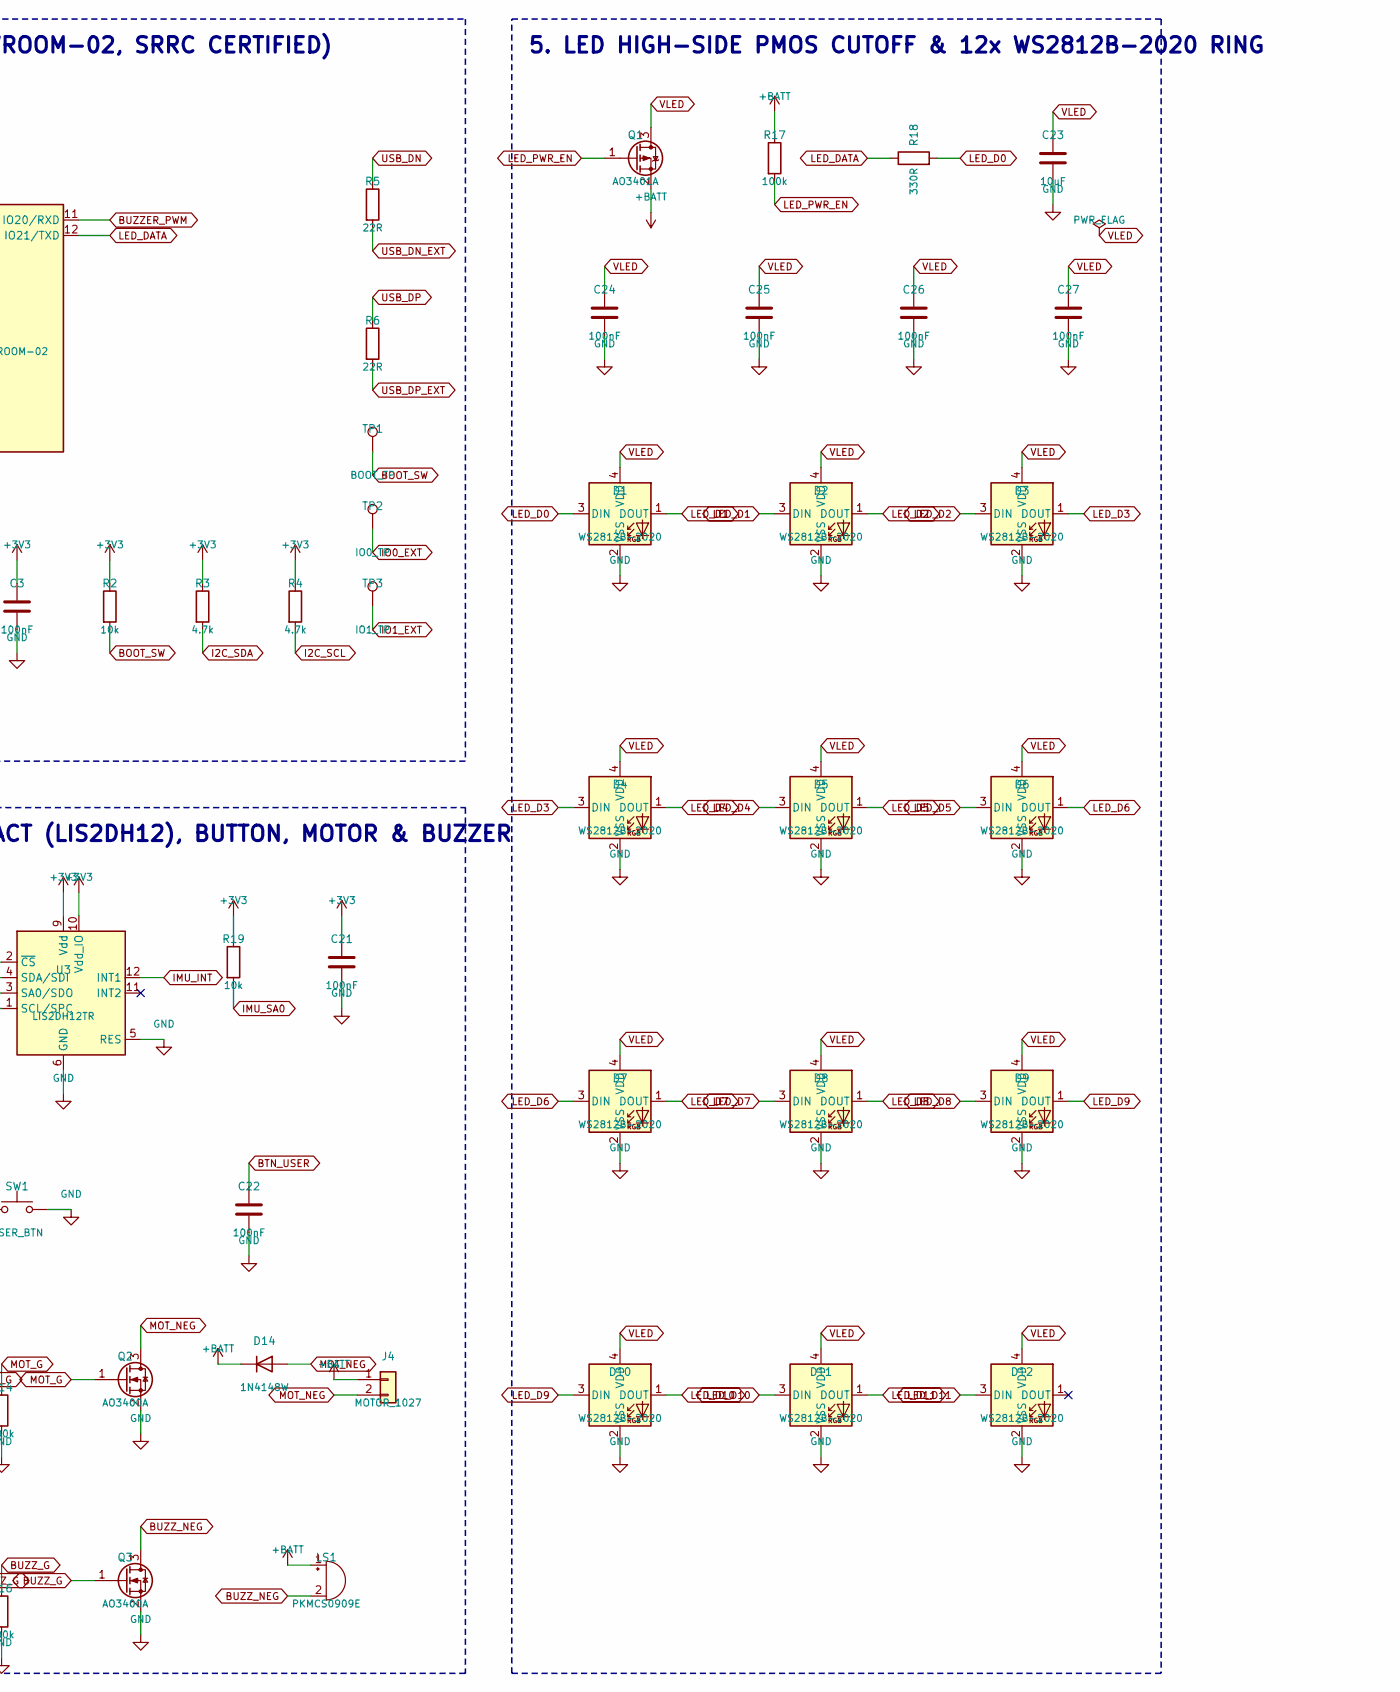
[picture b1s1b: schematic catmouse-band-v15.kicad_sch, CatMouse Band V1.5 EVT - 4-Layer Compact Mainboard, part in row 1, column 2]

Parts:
C1: 1uF; C_0402_1005Metric
C2, C6, C23: 10uF; C_0603_1608Metric
C3, C7, C8, C10, C11, C12, C13, C21, C22, C24, C25, C26, C27: 100nF; C_0402_1005Metric
C4, C5, C9: 4.7uF; C_0402_1005Metric
C14, C15: 22pF; C_0402_1005Metric
C16, C17: 150pF; C_0402_1005Metric
C18, C19: 47pF; C_0402_1005Metric
C20: 1nF; C_0402_1005Metric
D1, D2, D3, D4, D5, D6, D7, D8, D9, D10, D11, D12: WS2812B-2020; LED_WS2812B-2020_PLCC4_2.0x2.0mm
D13: RED_CHG; LED_0603_1608Metric
D14: 1N4148W; D_SOD-323
J1: MAG_CHG_USB; PinHeader_1x04_P2.54mm_Vertical_SMD_Pin1Left
J2: BAT_300mAh; JST_SH_SM02B-SRSS-TB_1x02-1MP_P1.00mm_Horizontal
J3: NFC_FPC_COIL; JST_SH_SM02B-SRSS-TB_1x02-1MP_P1.00mm_Horizontal
J4: MOTOR_1027; JST_SH_SM02B-SRSS-TB_1x02-1MP_P1.00mm_Horizontal
L1, L2: 560nH; L_0603_1608Metric
LS1: PKMCS0909E; Buzzer_Murata_PKMCS0909E
Q1: AO3401A; SOT-23
Q2, Q3: AO3400A; SOT-23
R1, R2, R11, R19: 10k; R_0402_1005Metric
R3, R4: 4.7k; R_0402_1005Metric
R5, R6: 22R; R_0402_1005Metric
R7: 3.3k; R_0402_1005Metric
R8, R12: 1k; R_0402_1005Metric
R9, R10: 200k 1%; R_0402_1005Metric
R13, R15: 100R; R_0402_1005Metric
R14, R16, R17: 100k; R_0402_1005Metric
R18: 330R; R_0402_1005Metric
SW1: USER_BTN; SW_SPST_B3U-1000P
TP1: BOOT_TP; TestPoint_Pad_D1.5mm
TP2: IO0_TP; TestPoint_Pad_D1.5mm
TP3: IO1_TP; TestPoint_Pad_D1.5mm
U1: ESP32-C3-WROOM-02
U2: PN5321A3HN; HVQFN-40-1EP_6x6mm_P0.5mm_EP4.1x4.1mm
U3: LIS2DH12TR; LGA-12_2x2mm_P0.5mm
U4: MCP73831-2-OT; SOT-23-5
U5: AP2112K-3.3; SOT-23-5
Y1: 27.12MHz; Crystal_SMD_3225-4Pin_3.2x2.5mm

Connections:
+3V3: C2.1, C3.1, C6.1, C7.1, C9.1, C10.1, C11.1, C21.1, R1.1, R2.1, R3.1, R4.1, R11.1, R19.1, U1.1 (3V3), U2.5 (TVDD), U2.8 (AVDD), U2.16 (I0), U2.23 (PVDD), U2.40 (VBAT), U3.2 (~CS), U3.9 (Vdd), U3.10 (Vdd_IO), U5.5 (VOUT)
+BATT: C5.1, D14.1 (K), J2.1, J4.1, LS1.1 (+), Q1.2 (S), R9.1, R17.1, U4.3 (V_{BAT}), U5.1 (VIN), U5.3 (EN)
BATT_ADC: C8.1, R9.2, R10.1, U1.16 (IO2)
BOOT_SW: R2.2, TP1.1, U1.8 (IO9)
BTN_USER: C22.1, SW1.1, U1.3 (IO4)
BUZZER_PWM: R15.1, U1.11 (IO20/RXD)
BUZZ_G: Q3.1 (G), R15.2, R16.1
BUZZ_NEG: LS1.2 (-), Q3.3 (D)
CHG_LED_A: D13.2 (A), R8.2
CHG_PROG: R7.1, U4.5 (PROG)
CHG_STAT: D13.1 (K), U4.1 (STAT)
ESP_EN: C1.1, R1.2, U1.2 (EN)
I2C_SCL: R4.2, U1.6 (IO7), U2.27 (NSS/P50_SCL/HSU_RX), U3.1 (SCL/SPC)
I2C_SDA: R3.2, U1.5 (IO6), U2.28 (MOSI/SDA/HSU_TX), U3.4 (SDA/SDI)
IMU_INT: U1.15 (IO3), U3.12 (INT1)
IMU_SA0: R19.2, U3.3 (SA0/SDO)
IO0_EXT: TP2.1, U1.18 (IO0)
IO1_EXT: TP3.1, U1.17 (IO1)
LED_D0: D1.3 (DIN), R18.2
LED_D1: D1.1 (DOUT), D2.3 (DIN)
LED_D2: D2.1 (DOUT), D3.3 (DIN)
LED_D3: D3.1 (DOUT), D4.3 (DIN)
LED_D4: D4.1 (DOUT), D5.3 (DIN)
LED_D5: D5.1 (DOUT), D6.3 (DIN)
LED_D6: D6.1 (DOUT), D7.3 (DIN)
LED_D7: D7.1 (DOUT), D8.3 (DIN)
LED_D8: D8.1 (DOUT), D9.3 (DIN)
LED_D9: D9.1 (DOUT), D10.3 (DIN)
LED_D10: D10.1 (DOUT), D11.3 (DIN)
LED_D11: D11.1 (DOUT), D12.3 (DIN)
LED_DATA: R18.1, U1.12 (IO21/TXD)
LED_PWR_EN: Q1.1 (G), R17.2, U1.7 (IO8)
MOTOR_PWM: R13.1, U1.4 (IO5)
MOT_G: Q2.1 (G), R13.2, R14.1
MOT_NEG: D14.2 (A), J4.2, Q2.3 (D)
NFC_ANT1: C18.2, J3.1
NFC_ANT2: C19.2, J3.2
NFC_DVDD: C12.1, U2.39 (DVDD)
NFC_EMC1: C16.1, C18.1, C20.1, L1.2
NFC_EMC2: C17.1, C19.1, L2.2
NFC_OSCIN: C14.1, U2.14 (OSCIN), Y1.1
NFC_OSCOUT: C15.1, U2.15 (OSCOUT), Y1.3
NFC_RST: R11.2, U1.10 (IO10), U2.38 (~RSTPD)
NFC_RX: R12.2, U2.10 (RX)
NFC_RX_MID: C20.2, R12.1
NFC_TX1: L1.1, U2.4 (TX1)
NFC_TX2: L2.1, U2.6 (TX2)
NFC_VMID: C13.1, U2.9 (VMID)
USB_DN: R5.1, U1.13 (IO18)
USB_DN_EXT: J1.3, R5.2
USB_DP: R6.1, U1.14 (IO19)
USB_DP_EXT: J1.4, R6.2

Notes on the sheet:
1. POWER, MAGNETIC CHARGING (USB) & BATTERY ADC
2. MCU CORE (ESP32-C3-WROOM-02, SRRC CERTIFIED)
3. DUAL-MODE NFC (PN5321A3HN I2C + 27.12MHz + 13.56MHz MATCHING)
4. IMU IMPACT (LIS2DH12), BUTTON, MOTOR & BUZZER
5. LED HIGH-SIDE PMOS CUTOFF & 12x WS2812B-2020 RING

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
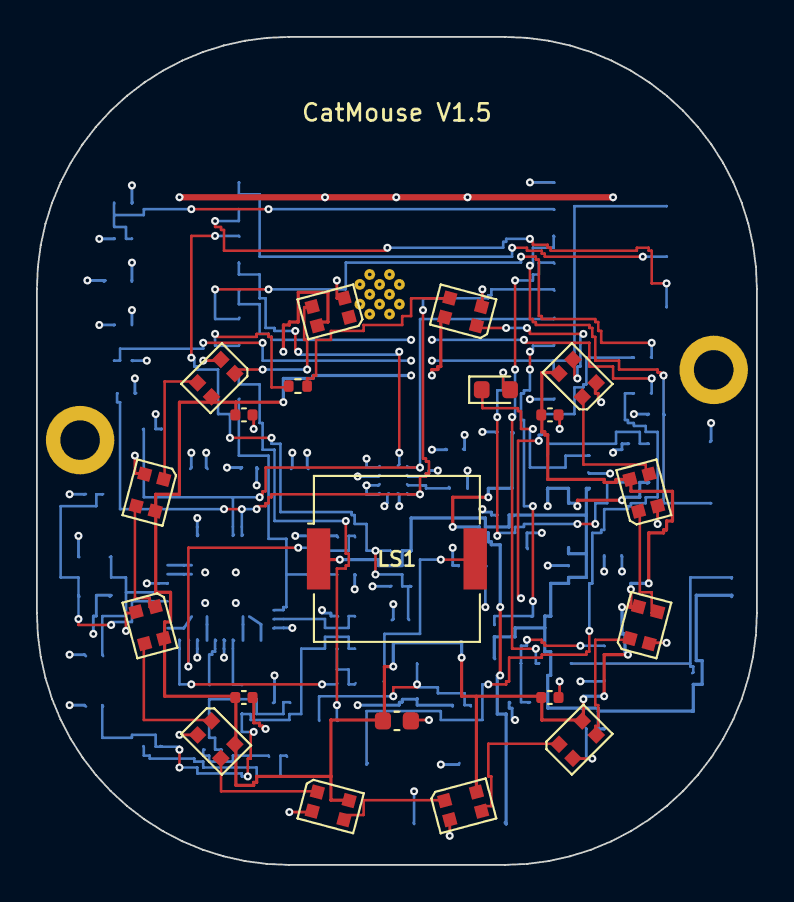
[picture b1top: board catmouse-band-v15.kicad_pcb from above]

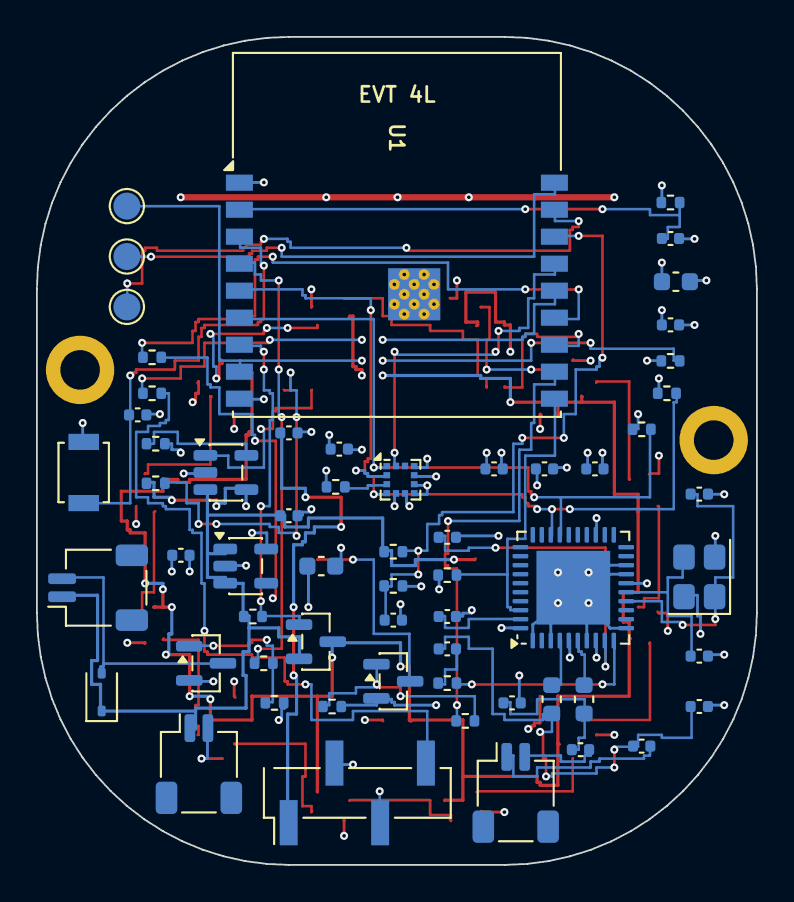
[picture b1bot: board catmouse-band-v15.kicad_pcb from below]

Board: 4 copper layers, 40.0 x 46.0 mm, 82 parts (60 on the bottom side), 55 nets.

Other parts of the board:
H1, H2: MountingHole_M2_GND; MountingHole_2.2mm_M2_DIN965_Pad

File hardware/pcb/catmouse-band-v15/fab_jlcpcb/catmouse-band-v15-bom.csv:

"Refs","Value","Footprint","Qty","DNP"
"C1","1uF","Capacitor_SMD:C_0402_1005Metric","1",""
"C2","10uF","Capacitor_SMD:C_0603_1608Metric","1",""
"C3","100nF","Capacitor_SMD:C_0402_1005Metric","1",""
"C4","4.7uF","Capacitor_SMD:C_0402_1005Metric","1",""
"C5","4.7uF","Capacitor_SMD:C_0402_1005Metric","1",""
"C6","10uF","Capacitor_SMD:C_0603_1608Metric","1",""
"C7","100nF","Capacitor_SMD:C_0402_1005Metric","1",""
"C8","100nF","Capacitor_SMD:C_0402_1005Metric","1",""
"C9","4.7uF","Capacitor_SMD:C_0402_1005Metric","1",""
"C10","100nF","Capacitor_SMD:C_0402_1005Metric","1",""
"C11","100nF","Capacitor_SMD:C_0402_1005Metric","1",""
"C12","100nF","Capacitor_SMD:C_0402_1005Metric","1",""
"C13","100nF","Capacitor_SMD:C_0402_1005Metric","1",""
"C14","22pF","Capacitor_SMD:C_0402_1005Metric","1",""
"C15","22pF","Capacitor_SMD:C_0402_1005Metric","1",""
"C16","150pF","Capacitor_SMD:C_0402_1005Metric","1",""
"C17","150pF","Capacitor_SMD:C_0402_1005Metric","1",""
"C18","47pF","Capacitor_SMD:C_0402_1005Metric","1",""
"C19","47pF","Capacitor_SMD:C_0402_1005Metric","1",""
"C20","1nF","Capacitor_SMD:C_0402_1005Metric","1",""
"C21","100nF","Capacitor_SMD:C_0402_1005Metric","1",""
"C22","100nF","Capacitor_SMD:C_0402_1005Metric","1",""
"C23","10uF","Capacitor_SMD:C_0603_1608Metric","1",""
"C24","100nF","Capacitor_SMD:C_0402_1005Metric","1",""
"C25","100nF","Capacitor_SMD:C_0402_1005Metric","1",""
"C26","100nF","Capacitor_SMD:C_0402_1005Metric","1",""
"C27","100nF","Capacitor_SMD:C_0402_1005Metric","1",""
"D1","WS2812B-2020","LED_SMD:LED_WS2812B-2020_PLCC4_2.0x2.0mm","1",""
"D2","WS2812B-2020","LED_SMD:LED_WS2812B-2020_PLCC4_2.0x2.0mm","1",""
"D3","WS2812B-2020","LED_SMD:LED_WS2812B-2020_PLCC4_2.0x2.0mm","1",""
"D4","WS2812B-2020","LED_SMD:LED_WS2812B-2020_PLCC4_2.0x2.0mm","1",""
"D5","WS2812B-2020","LED_SMD:LED_WS2812B-2020_PLCC4_2.0x2.0mm","1",""
"D6","WS2812B-2020","LED_SMD:LED_WS2812B-2020_PLCC4_2.0x2.0mm","1",""
"D7","WS2812B-2020","LED_SMD:LED_WS2812B-2020_PLCC4_2.0x2.0mm","1",""
"D8","WS2812B-2020","LED_SMD:LED_WS2812B-2020_PLCC4_2.0x2.0mm","1",""
"D9","WS2812B-2020","LED_SMD:LED_WS2812B-2020_PLCC4_2.0x2.0mm","1",""
"D10","WS2812B-2020","LED_SMD:LED_WS2812B-2020_PLCC4_2.0x2.0mm","1",""
"D11","WS2812B-2020","LED_SMD:LED_WS2812B-2020_PLCC4_2.0x2.0mm","1",""
"D12","WS2812B-2020","LED_SMD:LED_WS2812B-2020_PLCC4_2.0x2.0mm","1",""
"D13","RED_CHG","LED_SMD:LED_0603_1608Metric","1",""
"D14","1N4148W","Diode_SMD:D_SOD-323","1",""
"J1","MAG_CHG_USB","Connector_PinHeader_2.54mm:PinHeader_1x04_P2.54mm_Vertical_SMD_Pin1Left","1",""
"J2","BAT_300mAh","Connector_JST:JST_SH_SM02B-SRSS-TB_1x02-1MP_P1.00mm_Horizontal","1",""
"J3","NFC_FPC_COIL","Connector_JST:JST_SH_SM02B-SRSS-TB_1x02-1MP_P1.00mm_Horizontal","1",""
"J4","MOTOR_1027","Connector_JST:JST_SH_SM02B-SRSS-TB_1x02-1MP_P1.00mm_Horizontal","1",""
"L1","560nH","Inductor_SMD:L_0603_1608Metric","1",""
"L2","560nH","Inductor_SMD:L_0603_1608Metric","1",""
"LS1","PKMCS0909E","Buzzer_Beeper:Buzzer_Murata_PKMCS0909E","1",""
"Q1","AO3401A","Package_TO_SOT_SMD:SOT-23","1",""
"Q2","AO3400A","Package_TO_SOT_SMD:SOT-23","1",""
"Q3","AO3400A","Package_TO_SOT_SMD:SOT-23","1",""
"R1","10k","Resistor_SMD:R_0402_1005Metric","1",""
"R2","10k","Resistor_SMD:R_0402_1005Metric","1",""
"R3","4.7k","Resistor_SMD:R_0402_1005Metric","1",""
"R4","4.7k","Resistor_SMD:R_0402_1005Metric","1",""
"R5","22R","Resistor_SMD:R_0402_1005Metric","1",""
"R6","22R","Resistor_SMD:R_0402_1005Metric","1",""
"R7","3.3k","Resistor_SMD:R_0402_1005Metric","1",""
"R8","1k","Resistor_SMD:R_0402_1005Metric","1",""
"R9","200k 1%","Resistor_SMD:R_0402_1005Metric","1",""
"R10","200k 1%","Resistor_SMD:R_0402_1005Metric","1",""
"R11","10k","Resistor_SMD:R_0402_1005Metric","1",""
"R12","1k","Resistor_SMD:R_0402_1005Metric","1",""
"R13","100R","Resistor_SMD:R_0402_1005Metric","1",""
"R14","100k","Resistor_SMD:R_0402_1005Metric","1",""
"R15","100R","Resistor_SMD:R_0402_1005Metric","1",""
"R16","100k","Resistor_SMD:R_0402_1005Metric","1",""
"R17","100k","Resistor_SMD:R_0402_1005Metric","1",""
"R18","330R","Resistor_SMD:R_0402_1005Metric","1",""
"R19","10k","Resistor_SMD:R_0402_1005Metric","1",""
"SW1","USER_BTN","Button_Switch_SMD:SW_SPST_B3U-1000P","1",""
"TP1","BOOT_TP","TestPoint:TestPoint_Pad_D1.5mm","1",""
"TP2","IO0_TP","TestPoint:TestPoint_Pad_D1.5mm","1",""
"TP3","IO1_TP","TestPoint:TestPoint_Pad_D1.5mm","1",""
"U1","ESP32-C3-WROOM-02","RF_Module:ESP32-C3-WROOM-02","1",""
"U2","PN5321A3HN","Package_DFN_QFN:HVQFN-40-1EP_6x6mm_P0.5mm_EP4.1x4.1mm","1",""
"U3","LIS2DH12TR","Package_LGA:LGA-12_2x2mm_P0.5mm","1",""
"U4","MCP73831-2-OT","Package_TO_SOT_SMD:SOT-23-5","1",""
"U5","AP2112K-3.3","Package_TO_SOT_SMD:SOT-23-5","1",""
"Y1","27.12MHz","Crystal:Crystal_SMD_3225-4Pin_3.2x2.5mm","1",""
